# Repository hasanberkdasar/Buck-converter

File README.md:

# XL4015 USB Buck Converter

**An amateur/prototype DC-DC buck converter that provides a 5 V USB-A output from an 8–30 V DC input.**

This project is a PCB prototype developed by an Electrical and Electronics Engineering student for learning, design practice, and open-source sharing. The XL4015-based circuit steps a higher DC input voltage down to a regulated 5 V level suitable for a USB-A power output.

> [!WARNING]
> This board is an **amateur prototype** and has not been certified for safety-critical, commercial, or unattended applications. ERC checks for the schematic and DRC checks for the PCB were completed with **0 errors**. However, this does not mean the design is complete or error-free: there may still be overlooked issues related to connectivity, footprints, component selection, thermal behavior, EMI, or manufacturing. Independently verify the schematic, manufacturing files, and real measurements for your own application before using the board. All use is at the user's own risk.

## Design summary

| Feature | Value / status |
| --- | --- |
| Converter type | Asynchronous buck (step-down) |
| Controller IC | XL4015 / XL4015E1 |
| Recommended input | 8–30 V DC |
| IC operating range | 8–36 V DC |
| Target output | 5 V DC, USB-A VBUS |
| Feedback setting | R1 = 3.3 kΩ, R2 = 1.1 kΩ → approximately 5.0 V |
| ERC / DRC | 0 errors during the design stage |
| Status | Prototype; do not claim a continuous-current rating until it is validated with real load, temperature, and ripple tests |

For the XL4015, 40 V is an **absolute maximum rating**, not an operating voltage. The intended input range for this design is therefore 8–30 V. In addition, the fitted **SS54 diode has a 40 V reverse-voltage rating**, so this component is not suitable for 36 V or 40 V input. If a higher input voltage is required, select all relevant components—starting with the diode—with adequate voltage margin.

## How the circuit works

The DC input enters through the J1 terminal. The input capacitors support transient current demand and help reduce switching noise. The XL4015 drives its internal switch at approximately 180 kHz. D1 is the freewheeling diode that provides a path for the inductor current when the switch turns off. L1 and the output capacitor filter the switching waveform to produce a 5 V USB output.

The R1/R2 feedback divider sets the output voltage:

`VOUT ≈ 1.25 V × (1 + R1 / R2)`

`VOUT ≈ 1.25 V × (1 + 3.3 kΩ / 1.1 kΩ) = 5.0 V`

## Components and why they are used

| Reference | Part / value | Purpose and selection rationale |
| --- | --- | --- |
| U1 | XL4015 / XL4015E1 | Wide-input, fixed-frequency buck regulator IC intended for higher-current applications. |
| J1 | 2-pin screw terminal | Provides a robust, convenient DC input connection. |
| J2 | USB-A female connector | Presents the regulated 5 V output through a USB connector. |
| L1 | 47 µH power inductor | Stores energy and filters output current/ripple. Its saturation-current rating should exceed the expected peak current, and its DCR should be low. |
| D1 | SS54 Schottky diode | Provides the freewheeling path in the asynchronous buck topology; the low forward voltage helps reduce loss. This choice limits the design to 8–30 V input; use a 60 V-or-higher diode for higher voltages. |
| C2 | 220 µF / 50 V electrolytic capacitor | Supports low-frequency input ripple and transient current demand. |
| C1 | 10 µF / 50 V | Provides additional input filtering/local bypassing. |
| C4 | 1 µF | Compensation capacitor for the XL4015 VC/compensation network. Confirm its value against the XL4015 application circuit being used. |
| C3 | 470 µF | Reduces output ripple and improves load-transient response. Its voltage rating must exceed the 5 V output. |
| R1 | 3.3 kΩ | VOUT-to-FB feedback resistor; sets the 5 V output together with R2. |
| R2 | 1.1 kΩ | FB-to-GND feedback resistor; sets the 5 V output together with R1. |

## Connections

### Input — J1

| J1 pin | Connection |
| --- | --- |
| 1 | Positive DC input, `VIN` |
| 2 | Input negative / `GND` |

Connect only **8–30 V DC** to the input. Before assembling or connecting power, always cross-check the physical connector orientation and `VIN/GND` markings against the schematic.

### Output — USB-A (J2)

| USB-A pin | Connection |
| --- | --- |
| 1 — VBUS | Regulated +5 V |
| 4 — GND | Common ground |
| 2 — D− | Not used in this design |
| 3 — D+ | Not used in this design |

This board supplies **5 V power** through USB-A. It does not implement BC 1.2, Apple, or USB-C PD charging identification on D+/D−, so phones and some other devices may limit the charging current they request.

## Known limitations and suggestions for the next revision

- The continuous output-current capability depends on inductor saturation current, diode loss, copper thickness, airflow, and IC temperature. 
- For operation near 30 V input, consider a TVS diode, fuse/PTC, and reverse-polarity protection for input transients.
- Keep high-current traces short and wide; make the switching loop between the XL4015, D1, and input capacitor as compact as possible.
- Keep the feedback divider away from the switching node and close to the output capacitor.
- Before fabrication, independently review Gerbers, drill files, footprints, polarities, and 3D mechanical clearances.

## Suggested test procedure

For first power-up, use a current-limited bench power supply. First verify that the no-load output is close to 5 V. Then use an electronic load in gradual steps to measure voltage regulation, ripple, input current, and the temperatures of the diode, inductor, and IC, as well as short-circuit behavior. Before connecting a USB device, check that there is no short circuit between VBUS and GND.

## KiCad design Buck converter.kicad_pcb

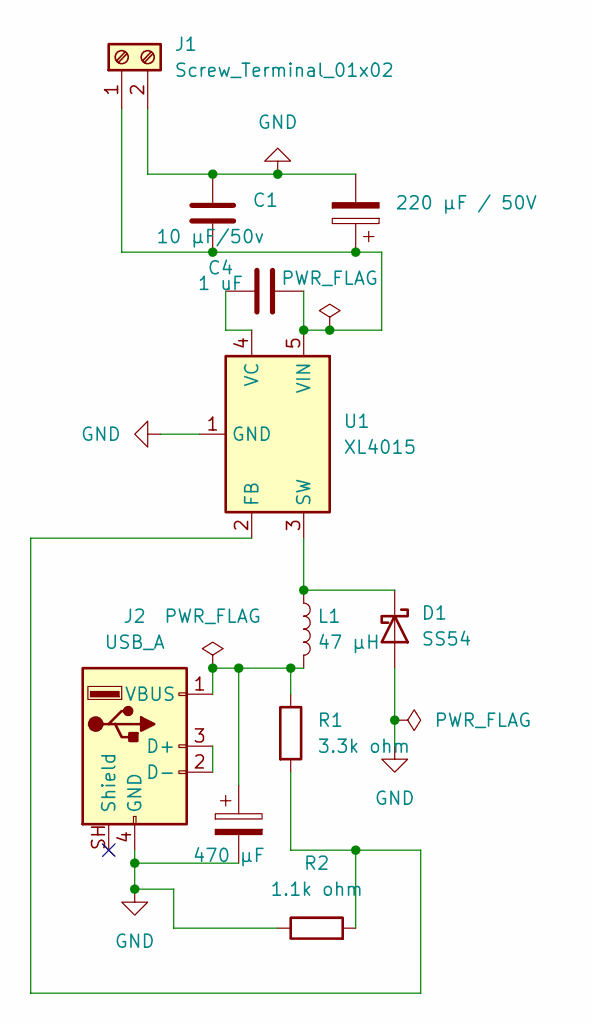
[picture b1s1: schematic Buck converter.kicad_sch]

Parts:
C1: 10 µF/50v; C_0805_2012Metric
C2: 220 µF / 50V; CP_Radial_D8.0mm_P3.50mm
C3: 470 µF; CP_Radial_D8.0mm_P3.50mm
C4: 1 uF; C_0805_2012Metric
D1: SS54; D_SMC
J1: Screw_Terminal_01x02; TerminalBlock_Phoenix_MKDS-1,5-2-5.08_1x02_P5.08mm_Horizont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
J2: USB_A; USB_A_Molex_67643_Horizontal
L1: 47 µH; L_12x12mm_H6mm
R1: 3.3k ohm; R_0805_2012Metric
R2: 1.1k ohm; R_0805_2012Metric
U1: XL4015; TO-263-5_TabPin3

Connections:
GND: C1.2, C2.2, C3.2, D1.2 (A), J1.2, J2.4 (GND), R2.1, U1.1 (GND)
unnamed: D1.1 (K), L1.1, U1.3 (SW)
unnamed: C1.1, C2.1, C4.2, J1.1, U1.5 (VIN)
unnamed: J2.2 (D-), J2.3 (D+)
unnamed: C3.1, J2.1 (VBUS), L1.2, R1.1
unnamed: R1.2, R2.2, U1.2 (FB)
unnamed: C4.1, U1.4 (VC)

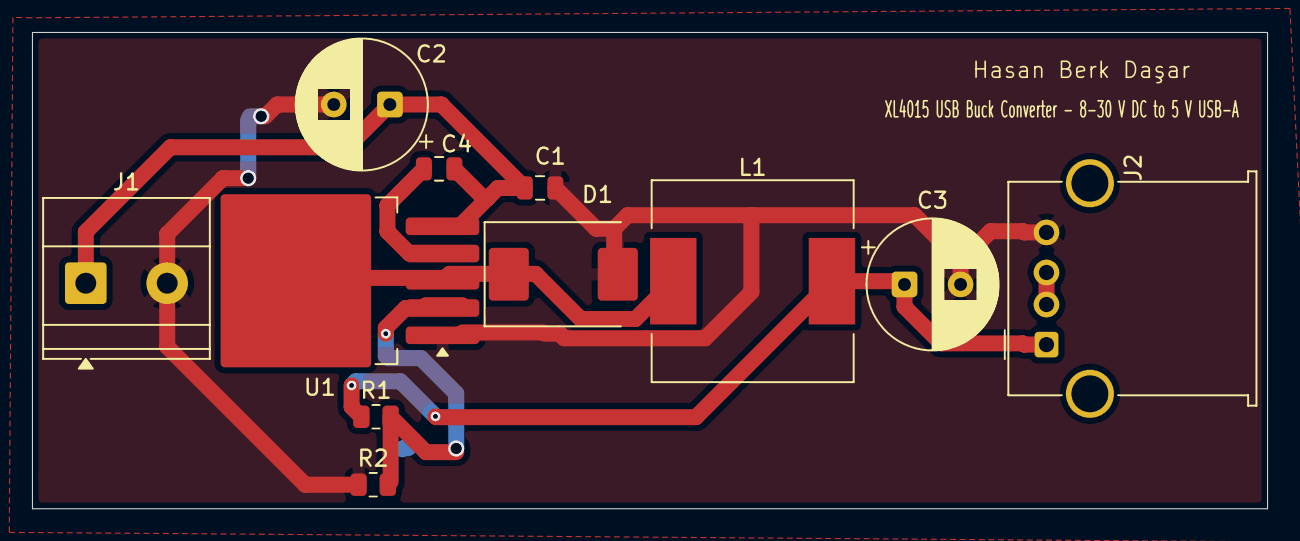
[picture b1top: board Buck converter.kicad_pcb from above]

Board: 2 copper layers, 77.1 x 29.7 mm, 11 parts (0 on the bottom side), 7 nets.
